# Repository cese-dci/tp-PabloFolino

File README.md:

# Circuitos Lógicos Programables
Materia:Diseño de Circuitos Impresos de la Especialización de Sistemas Embebidos de la FIUBA

Autor: Pablo D. Folino

Revisor: Sergio Alberino

Enlace --> https://github.com/cese-dci/tp-SergioAlberino/blob/master/Revisi%C3%B3n%20Folino/1.4.Plantilla%20de%20revisi%C3%B3n%20de%20PCBs%20-%20Folino.xlsx

Profesor: Diego Brengi

Año: 2021

# Historial del proyecto

| Fecha | Descripción | 
| :-: | :-: |
|[11/03/2021] | Creación del repositorio. | 
|[06/042021] | Generación del esquemático. | 
|[07/04/2021] | Chequeo del ERC del esquemàtico --> 3 Warnings. |
|[08/04/2021] | Actualización Esquemático Power_Flag -- > 0 Warnings. |
|[08/04/2021] | Modificación de la organización del repositorio. | 
|[09/04/2021] | Corrección de errores de documentación. | 
|[10/04/2021] | Actualiza Footprint D3. | 
|[11/04/2021] | Creación PCB, y modelo 3D de SSR. | 
|[14/04/2021] | Se realizan las correciones del esquemático propuestas por el profesor. | 
|[19/04/2021] | Se actualiza PCB. | 
 
# Revisiones del Profesor

| Item | Estado| 
| :-: | :-: |
|[Esquemático]FALTA. Colocar en el rótulo  una licencia libre como se acordó en las pautas del TP. | Se agrega en el rótulo la licencia. | 
|[Esquemático]Tal vez el símbolo de K1 y K2 podría reflejar ENTRADA y SALIDA en la posición de los terminales (izq y derecha). |  Se editó el componente para satisfacer lo solicitado.  |
|[Esquemático]"* Para los titulos de los bloques se utilió la herramienta de etiqueta local. Usar la de Texto.* No parece un buen nombre ""Componentes físicos"" ya que todos lo son. El título podría ser simplemente agujeros y fiduciales." |  Se cambio de etiquetas locales a Texto, y se cambió el nombre a Agujeros y Fiduciales.  |
|[Esquemático]"* Coloque un código de catálogo para C1 que es un componete importante y con características particulares. Tambíen de F1, F2 y D2 .* Debe poner un modelo de diodo para D1, D3.* Los resistores ya tienen referencias con la letra R. No hay que repetir la R en el campo valor (R10K). Solo 10K. La R se utiliza por ejemplo para un resistor de 10 Ohm, se pone 10 R (para no escribir la palabra Ohm ni poner la letra griega Omega).* Lo mismo para las capacitores. No es C100uF es 100uF.* La referencjia U (U1) se usa para circuitos integrados. Para Módulos se puede usar mejor XA (XA1) o XU (XU1). https://en.wikipedia.org/wiki/Reference_designator* El valor de F1 y F2 creo que no lleva espacio ya que es un código." | 1) se colocó Part-Number a C1,F1,F2,D1,D2, y D3, y en algunos casos el datasheet. 2) Se adecuó los valores de C y R según lo solicitado. 3) Se modificaó la referencia del módulo a XU1.  |
|[Esquemático]"* Tiene cargada mal una biblioteca de huellas que da error al cargar: Footprint library path ""/home/pablo/Documentos/Especialización/12_DCI/Proyectos/Library/Modelos_3D"". Las bibliotecas de huellas son directorios .pretty.* Aclaración: En este caso como es una placa TH, el fiducial no es muy necesario, pero puede dejarlo como una buena práctica. " |  Se deja el fiducial, se elimina la biblioteca.  |
|[Impreso] Mencionar la licencia o el link a la misma en el rótulo. | Se escreibe el link de la linencia en el rótulo. | 
|[Impreso] Dice margen de 0,25 pero en realidad es mayor. Actualizar la nota.| Se actuañiza margen a 0,50mm. | 
|[Impreso] Podría aclarar que el diseño es simple faz y que la capa TOP es de puentes.| Se agregan las notas correspondientes al diseño. | 
|[Impreso] Tal vez podría aplicar en algún sector un relleno para GND.| Se aplica relleno de cobre a todo el PCB. | 
|[Impreso] Los modelos tienen rutas absolutas. Intente que queden así: ${KIPRJMOD}/shapes3D/G3MB_202P.wrl| Se redireccionaron las librerìas. | 
|[Impreso] Si puede estaría bueno agregar el modelo del ESP-01. Ayuda a visualizar el resultado final. Se agrega como un modelo adicional a XU1."| Se creó modelo 3D del ESP. |

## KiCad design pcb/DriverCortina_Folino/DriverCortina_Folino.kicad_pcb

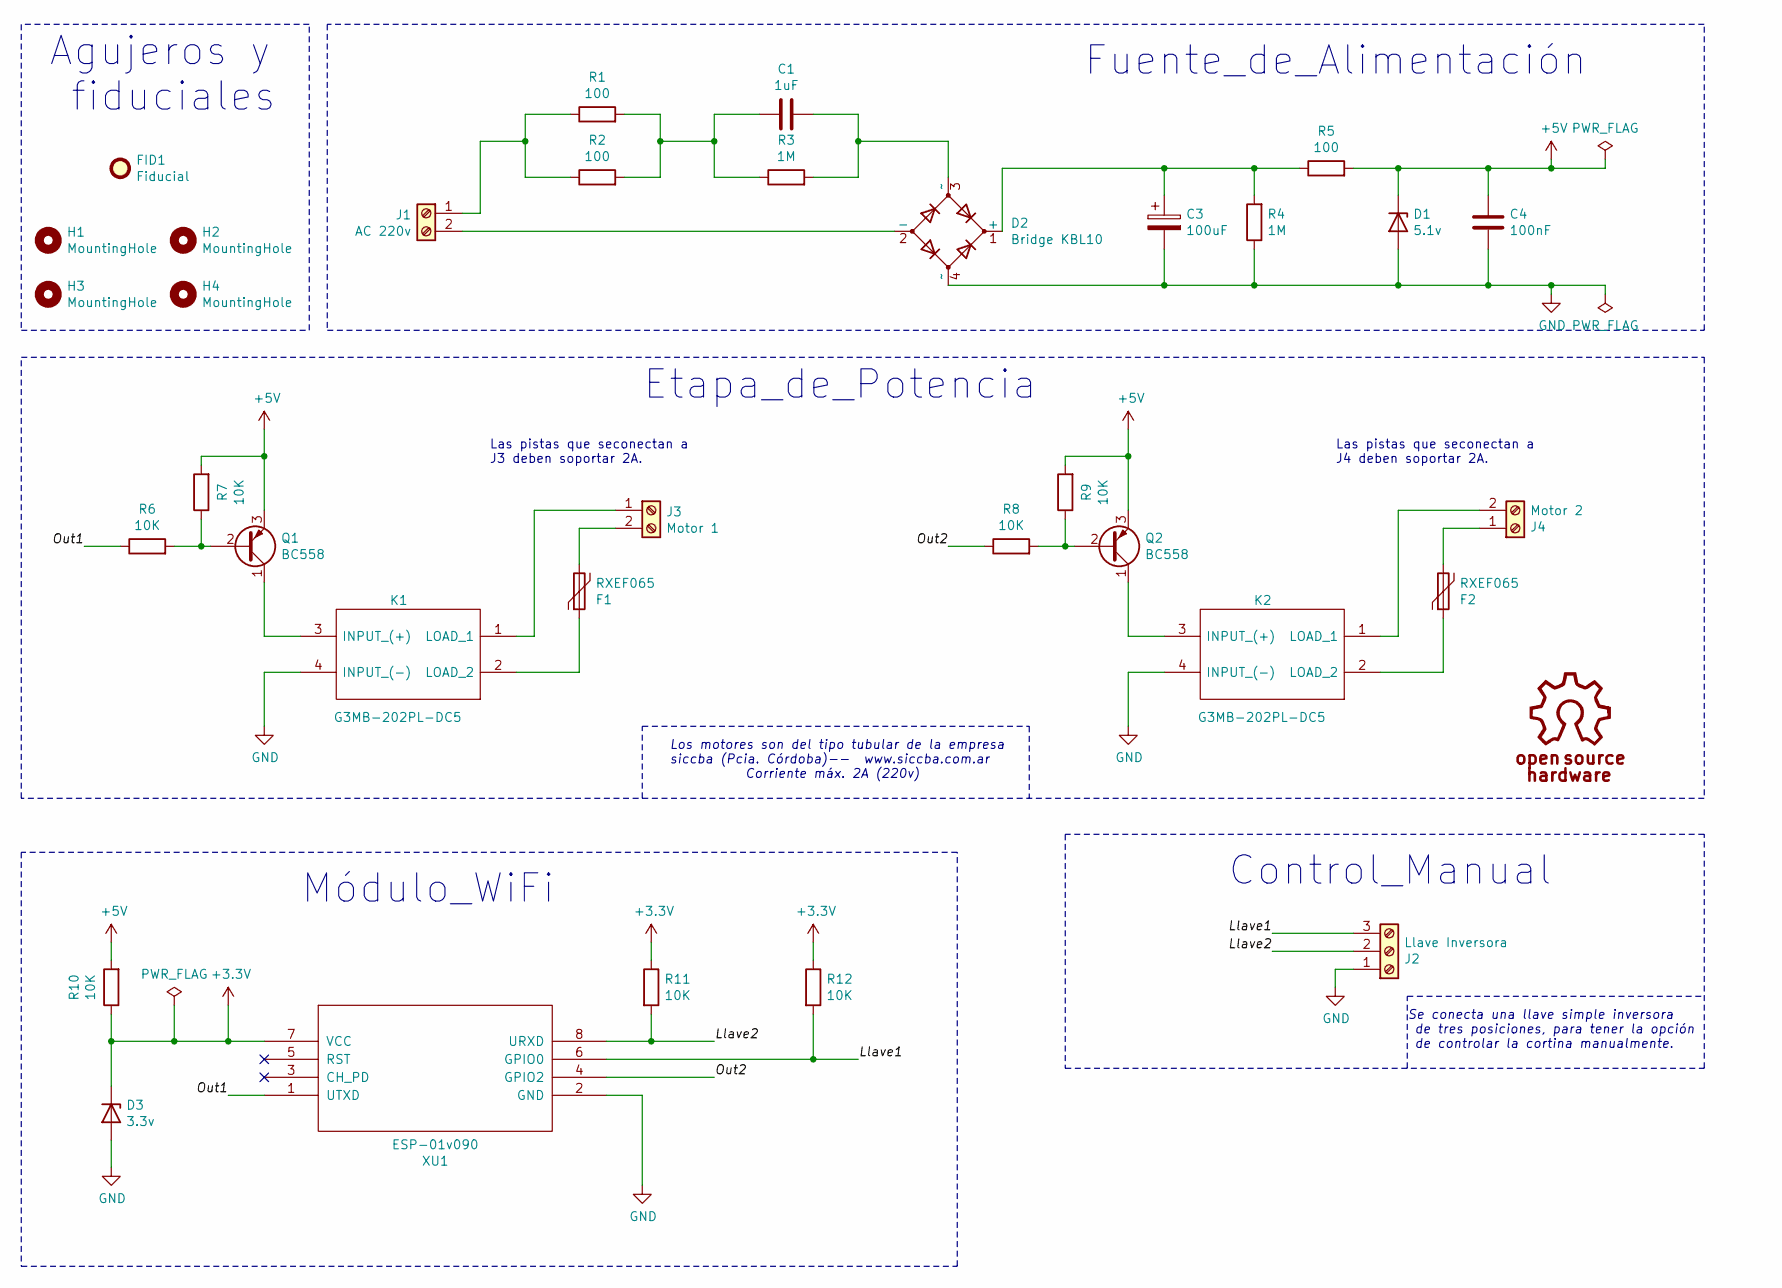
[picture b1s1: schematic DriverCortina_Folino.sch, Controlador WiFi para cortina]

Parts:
C1: 1uF; C_Rect_L26.5mm_W11.5mm_P22.50mm_MKS4; Manufacturer_Part_Number W42Q3105-P8*******
C3: 100uF; CP_Radial_D5.0mm_P2.50mm
C4: 100nF; C_Disc_D3.8mm_W2.6mm_P2.50mm; Manufacture_part_name C320C104K5R5TA
D1: 5.1v; D_DO-35_SOD27_P7.62mm_Horizontal; Manufacturer_Part_Number BZX55C5V1
D2: Bridge KBL10; Diode_Bridge_Vishay_KBL; Manufacturer_Part_Number KBL10
D3: 3.3v; D_DO-35_SOD27_P7.62mm_Horizontal; Manufacturer_Part_Number BZX55C3V3
F1, F2: RXEF065; C_Disc_D10.0mm_W2.5mm_P5.00mm; Manufacturer_Part_Number MF-R135-0-99
FID1: Fiducial; Fiducial_1.5mm_Mask3mm
H1, H2, H3, H4: MountingHole; MountingHole_2.5mm_Pad
J1: AC 220v; bornera_1x2_con_tornillo_5.08mm
J2: Llave Inversora; bornera_1x3_con_tornillo_5.08mm
J3: Motor 1; bornera_1x2_con_tornillo_5.08mm
J4: Motor 2; bornera_1x2_con_tornillo_5.08mm
K1, K2: G3MB-202PL-DC5; G3MB202PLDC5; Manufacturer_Part_Number G3MB-202PL-DC5; Mouser Part Number 653-G3MB-202PL-DC5
Q1, Q2: BC558; TO-92L_Inline_Wide; Manufacture_part_name BC558-ND
R1, R2, R5: 100; R_Axial_DIN0207_L6.3mm_D2.5mm_P10.16mm_Horizontal
R3, R4: 1M; R_Axial_DIN0207_L6.3mm_D2.5mm_P10.16mm_Horizontal
R6, R7, R8, R9, R10, R11, R12: 10K; R_Axial_DIN0207_L6.3mm_D2.5mm_P10.16mm_Horizontal
XU1: ESP-01v090; ESP-01

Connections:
+3V3: D3.1 (K), R10.1, R11.1, R12.1, XU1.7 (VCC)
+5V: C4.1, D1.1 (K), Q1.3 (E), Q2.3 (E), R5.2, R7.2, R9.2, R10.2
/Llave1: J2.3, R12.2, XU1.6 (GPIO0)
/Llave2: J2.2, R11.2, XU1.8 (URXD)
/Out1: R6.1, XU1.1 (UTXD)
/Out2: R8.1, XU1.4 (GPIO2)
GND: C3.2, C4.2, D1.2 (A), D2.4 (~~), D3.2 (A), J2.1, K1.4 (INPUT_(-)), K2.4 (INPUT_(-)), R4.1, XU1.2 (GND)
unnamed: C1.1, R1.2, R2.2, R3.1
unnamed: C1.2, D2.3 (~~), R3.2
unnamed: C3.1, D2.1 (+), R4.2, R5.1
unnamed: D2.2 (-), J1.2
unnamed: F1.1, K1.2 (LOAD_2)
unnamed: F1.2, J3.2
unnamed: F2.1, K2.2 (LOAD_2)
unnamed: F2.2, J4.1
unnamed: J1.1, R1.1, R2.1
unnamed: J3.1, K1.1 (LOAD_1)
unnamed: J4.2, K2.1 (LOAD_1)
unnamed: K1.3 (INPUT_(+)), Q1.1 (C)
unnamed: K2.3 (INPUT_(+)), Q2.1 (C)
unnamed: Q1.2 (B), R6.2, R7.1
unnamed: Q2.2 (B), R8.2, R9.1

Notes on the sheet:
Se conecta una llave simple inversora de tres posiciones, para tener la opción de controlar la cortina manualmente.
Los motores son del tipo tubular de la empresa siccba (Pcia. Córdoba)-- www.siccba.com.ar Corriente máx. 2A (220v)
Las pistas que seconectan a J4 deben soportar 2A.
Las pistas que seconectan a J3 deben soportar 2A.
Etapa_de_Potencia
Control_Manual
Módulo_WiFi
Fuente_de_Alimentación
Agujeros y fiduciales

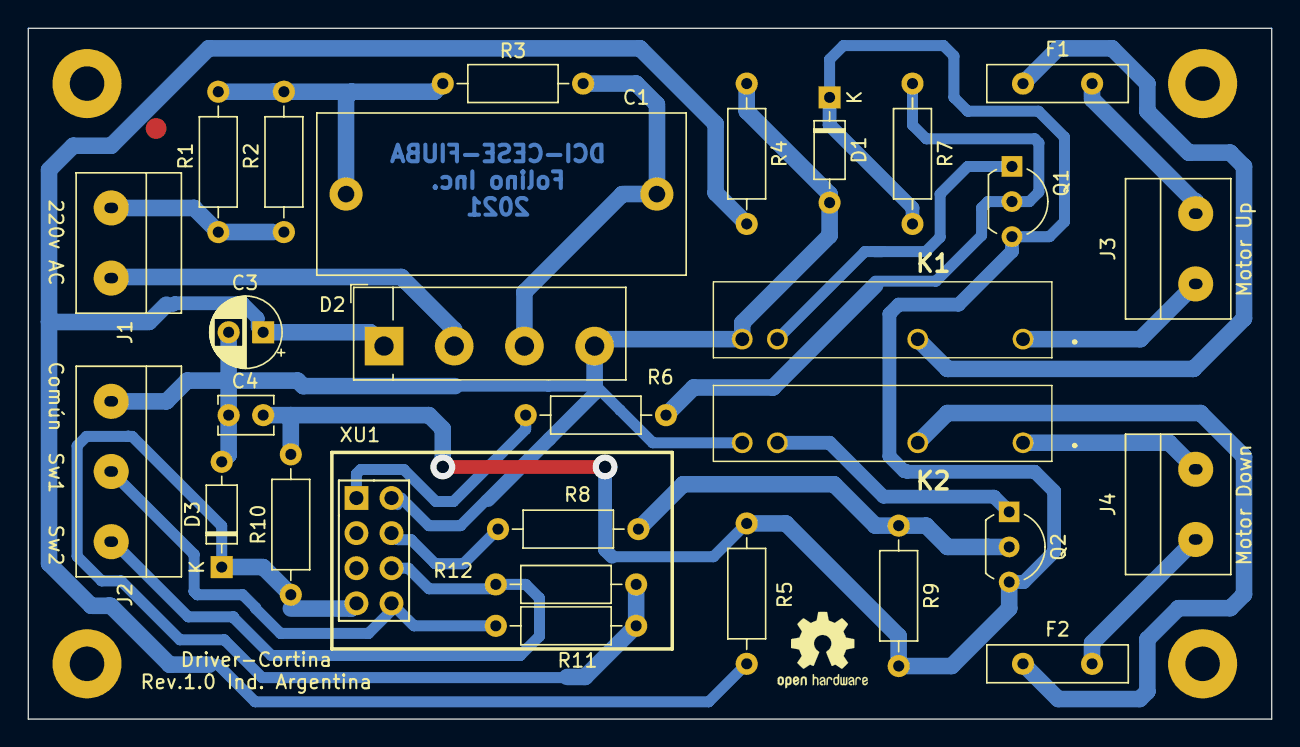
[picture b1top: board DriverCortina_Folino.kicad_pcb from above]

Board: 2 copper layers, 90.0 x 50.0 mm, 34 parts (0 on the bottom side), 22 nets.

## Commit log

2021-04-07 Esquemático y documentación
2021-04-07 Se actualiza documentación
2021-04-09 Actualización Esquemático Power_Flag
2021-04-09 Modificación de la organización del repositorio
2021-04-09 Corrección de errores de documentación
2021-04-10 Actualiza Footprint D3
2021-04-11 Creación PCB y modelo 3D de SSR
2021-04-14 Se realizan las correciones del esquemático.
2021-04-19 Se actualiza PCB
2021-04-22 Mejoras de PCB
2021-04-25 Se corrigen detalles del PCB

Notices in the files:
pcb/DriverCortina_Folino/DriverCortina_Folino.kicad_pcb:
Licencia: http://creativecommons.org/licenses/by/4.0
pcb/DriverCortina_Folino/DriverCortina_Folino.sch:
Licencia: CC BY 4.0
